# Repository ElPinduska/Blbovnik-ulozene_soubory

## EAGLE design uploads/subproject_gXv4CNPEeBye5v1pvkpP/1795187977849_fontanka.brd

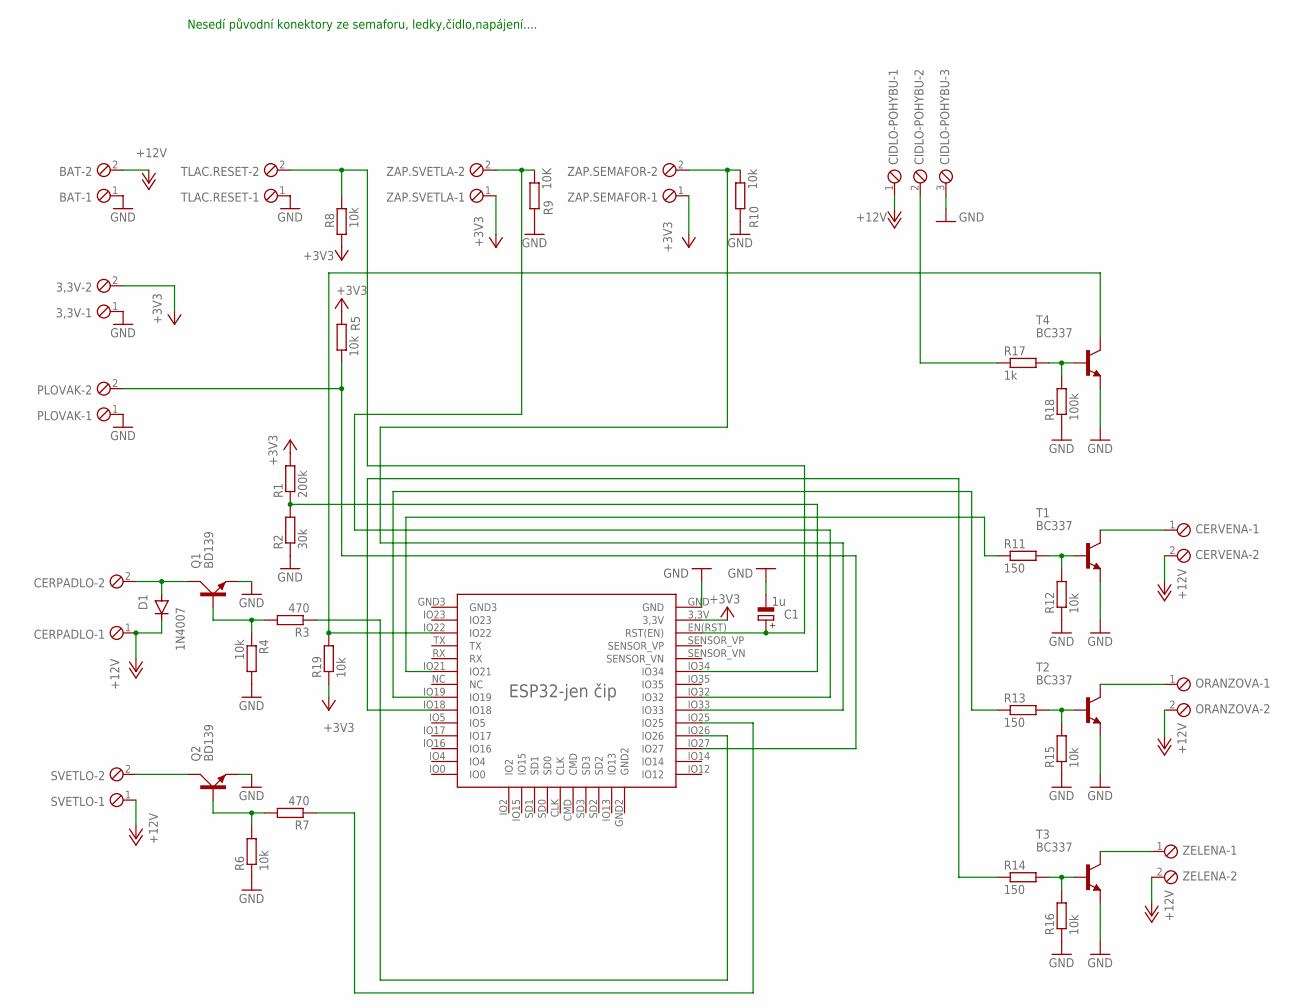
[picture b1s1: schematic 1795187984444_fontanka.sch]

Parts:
3,3V: MPT2; 2POL254
BAT: MPT2; 2POL254
C1: 1u; E2,5-6E
CERPADLO: MPT2; 2POL254
CERVENA: MPT2; 2POL254
CIDLO-POHYBU: MPT3; 3POL254
D1: 1N4007; DO41-10
ORANZOVA: MPT2; 2POL254
PLOVAK: MPT2; 2POL254
Q1, Q2: BD139; TO126AV
R1: 200k; 0204/7
R2: 30k; 0204/7
R3, R7: 470; 0204/7
R4, R5, R6, R8, R10, R12, R15, R16, R19: 10k; 0204/7
R9: 10K; 0204/7
R11, R13, R14: 150; 0204/7
R17: 1k; 0204/7
R18: 100k; 0204/7
SVETLO: MPT2; 2POL254
T1, T2, T3, T4: BC337; TO92-CBE
TLAC.RESET: MPT2; 2POL254
U$2: ESP32-PATICEESP32-2,54PIN; ESP32-PATICE2,54
ZAP.SEMAFOR, ZAP.SVETLA: MPT2; 2POL254
ZELENA: MPT2; 2POL254

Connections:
+3V3: 3,3V.2, R1.2, R5.2, R8.1, R19.1, U$2.3,3V, ZAP.SEMAFOR.1, ZAP.SVETLA.1
+12V: BAT.2, CERPADLO.1, CERVENA.2, CIDLO-POHYBU.1, D1.C, ORANZOVA.2, SVETLO.1, ZELENA.2
GND: 3,3V.1, BAT.1, C1.-, CIDLO-POHYBU.3, PLOVAK.1, Q1.E, Q2.E, R2.1, R4.2, R6.1, R9.1, R10.1, R12.1, R15.1, R16.1, R18.1, T1.E, T2.E, T3.E, T4.E, TLAC.RESET.1, U$2.GND
unnamed: R1.1, R2.2, U$2.IO34
unnamed: R3.1, U$2.IO26
unnamed: Q1.B, R3.2, R4.1
unnamed: CERPADLO.2, D1.A, Q1.C
unnamed: R19.2, T4.C, U$2.IO22
unnamed: R11.1, U$2.IO21
unnamed: PLOVAK.2, R5.1, U$2.IO27
unnamed: C1.+, R8.2, TLAC.RESET.2, U$2.EN(RST) (RST(EN))
unnamed: R7.1, U$2.IO25
unnamed: Q2.B, R6.2, R7.2
unnamed: R9.2, U$2.IO32, ZAP.SVETLA.2
unnamed: R10.2, U$2.IO33, ZAP.SEMAFOR.2
unnamed: R11.2, R12.2, T1.B
unnamed: R13.1, U$2.IO19
unnamed: R14.1, U$2.IO18
unnamed: R13.2, R15.2, T2.B
unnamed: R14.2, R16.2, T3.B
unnamed: T3.C, ZELENA.1
unnamed: ORANZOVA.1, T2.C
unnamed: CERVENA.1, T1.C
unnamed: R17.2, R18.2, T4.B
unnamed: CIDLO-POHYBU.2, R17.1
SVETLO: Q2.C, SVETLO.2

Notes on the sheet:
Nesedí původní konektory ze semaforu, ledky,čidlo,napájení....

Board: 2 copper layers, 40 parts (0 on the bottom side), 26 nets, no tracks yet.

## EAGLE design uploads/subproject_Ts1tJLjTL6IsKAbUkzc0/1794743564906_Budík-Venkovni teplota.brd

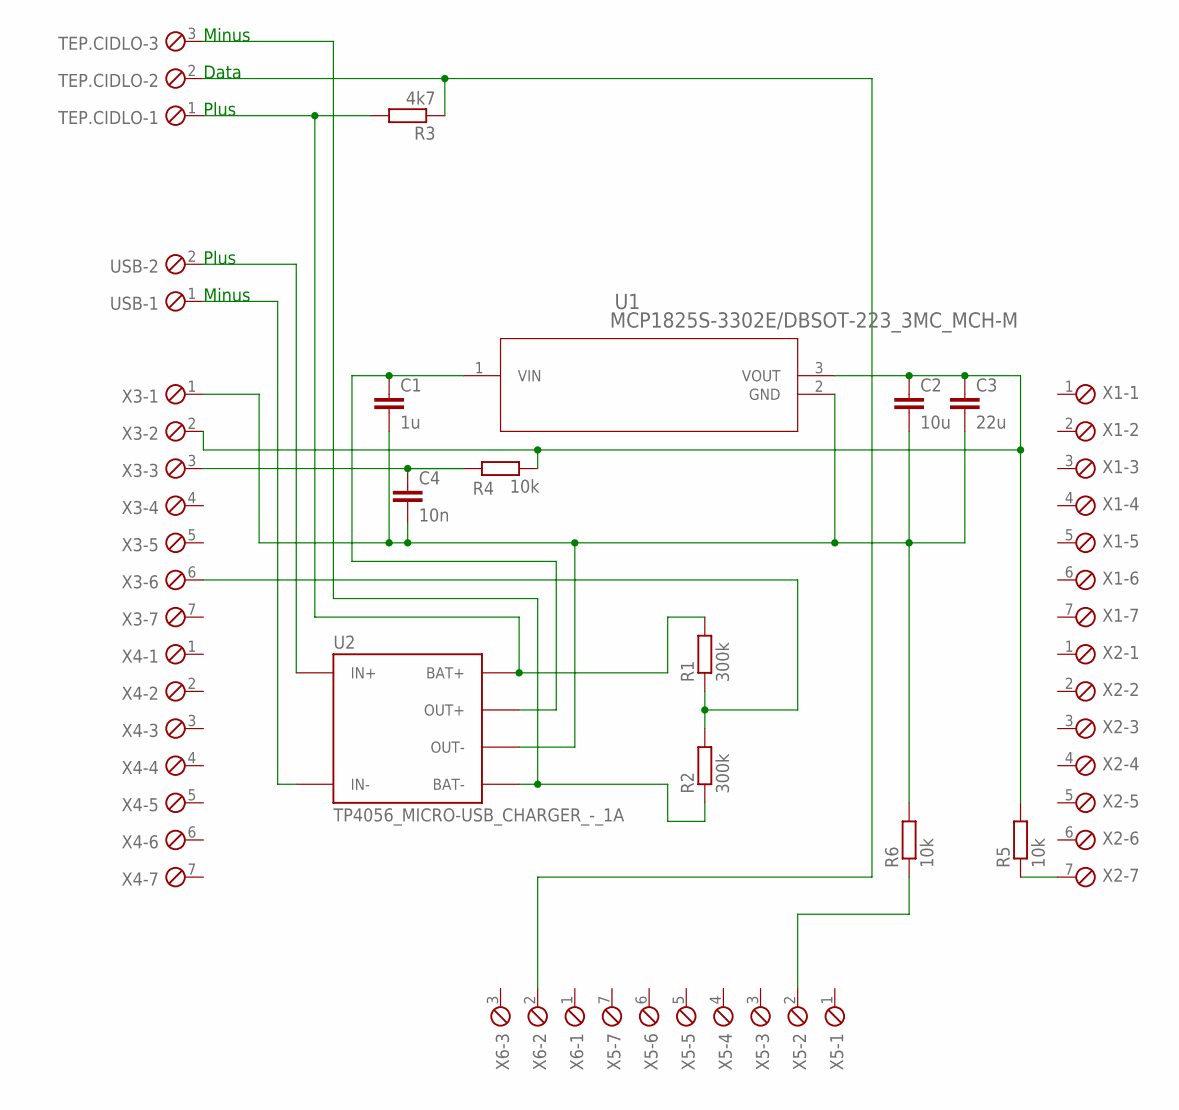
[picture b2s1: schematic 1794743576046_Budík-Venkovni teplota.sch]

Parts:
C1: 1u; C0805
C2: 10u; C0805
C3: 22u; C0805
C4: 10n; C0805
R1, R2: 300k; 0204/7
R3: 4k7; 0204/7
R4, R5, R6: 10k; 0204/7
TEP.CIDLO: MPT3; 3POL254
U1: MCP1825S-3302E/DBSOT-223_3MC_MCH-M; SOT-223_3MC_MCH-M
U2: TP4056_MICRO-USB_CHARGER_-_1A; MODULE_TP4056_MICRO-USB_CHARGER_-_1A
USB: MPT2; 2POL254
X1, X2, X3, X4, X5: MPT7; 7POL254
X6: MPT3; 3POL254

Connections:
unnamed: U2.IN_N (IN-), USB.1
unnamed: U2.IN_P (IN+), USB.2
unnamed: R1.2, R3.2, TEP.CIDLO.1, U2.BAT_P (BAT+)
unnamed: R2.1, TEP.CIDLO.3, U2.BAT_N (BAT-)
unnamed: C1.1, U1.1 (VIN), U2.OUT_P (OUT+)
unnamed: C1.2, C2.2, C3.2, C4.2, R6.2, U1.2 (GND), U2.OUT_N (OUT-), X3.1
unnamed: C2.1, C3.1, R4.2, R5.2, U1.3 (VOUT), X3.2
unnamed: R1.1, R2.2, X3.6
unnamed: R3.1, TEP.CIDLO.2, X6.2
unnamed: C4.1, R4.1, X3.3
unnamed: R5.1, X2.7
unnamed: R6.1, X5.2

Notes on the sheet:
Minus
Plus
Data

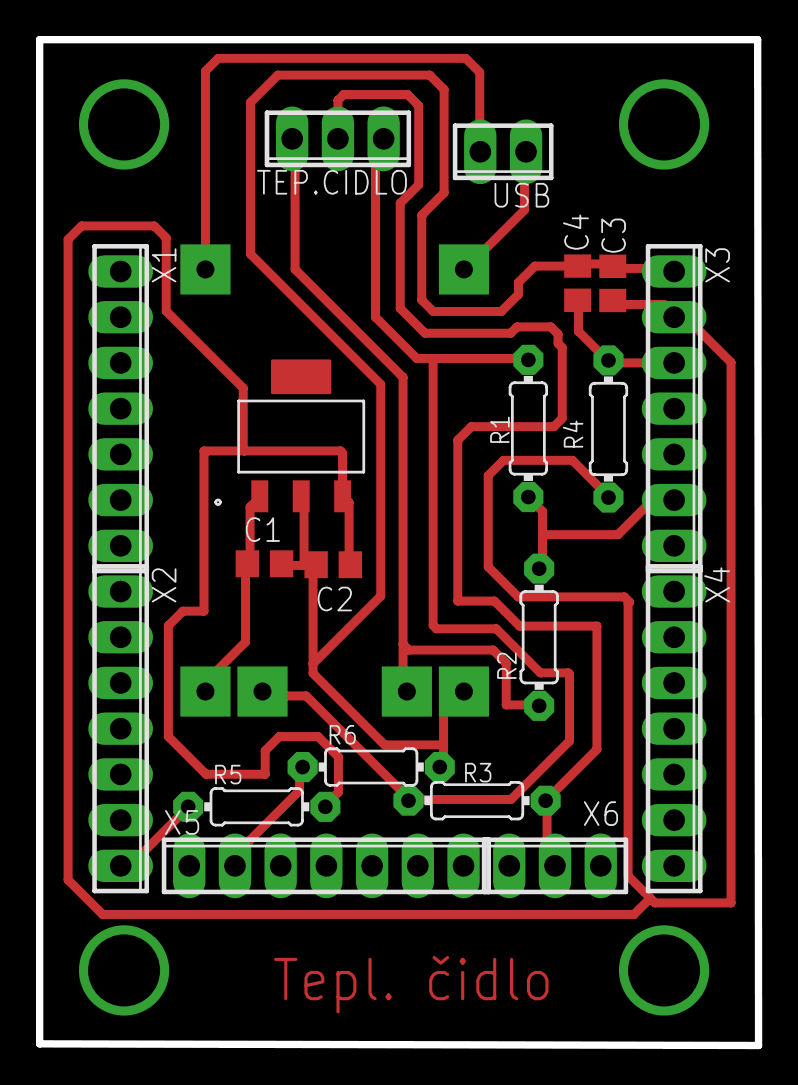
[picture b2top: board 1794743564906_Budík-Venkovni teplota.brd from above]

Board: 2 copper layers, 39.9 x 55.9 mm, 20 parts (1 on the bottom side), 12 nets.

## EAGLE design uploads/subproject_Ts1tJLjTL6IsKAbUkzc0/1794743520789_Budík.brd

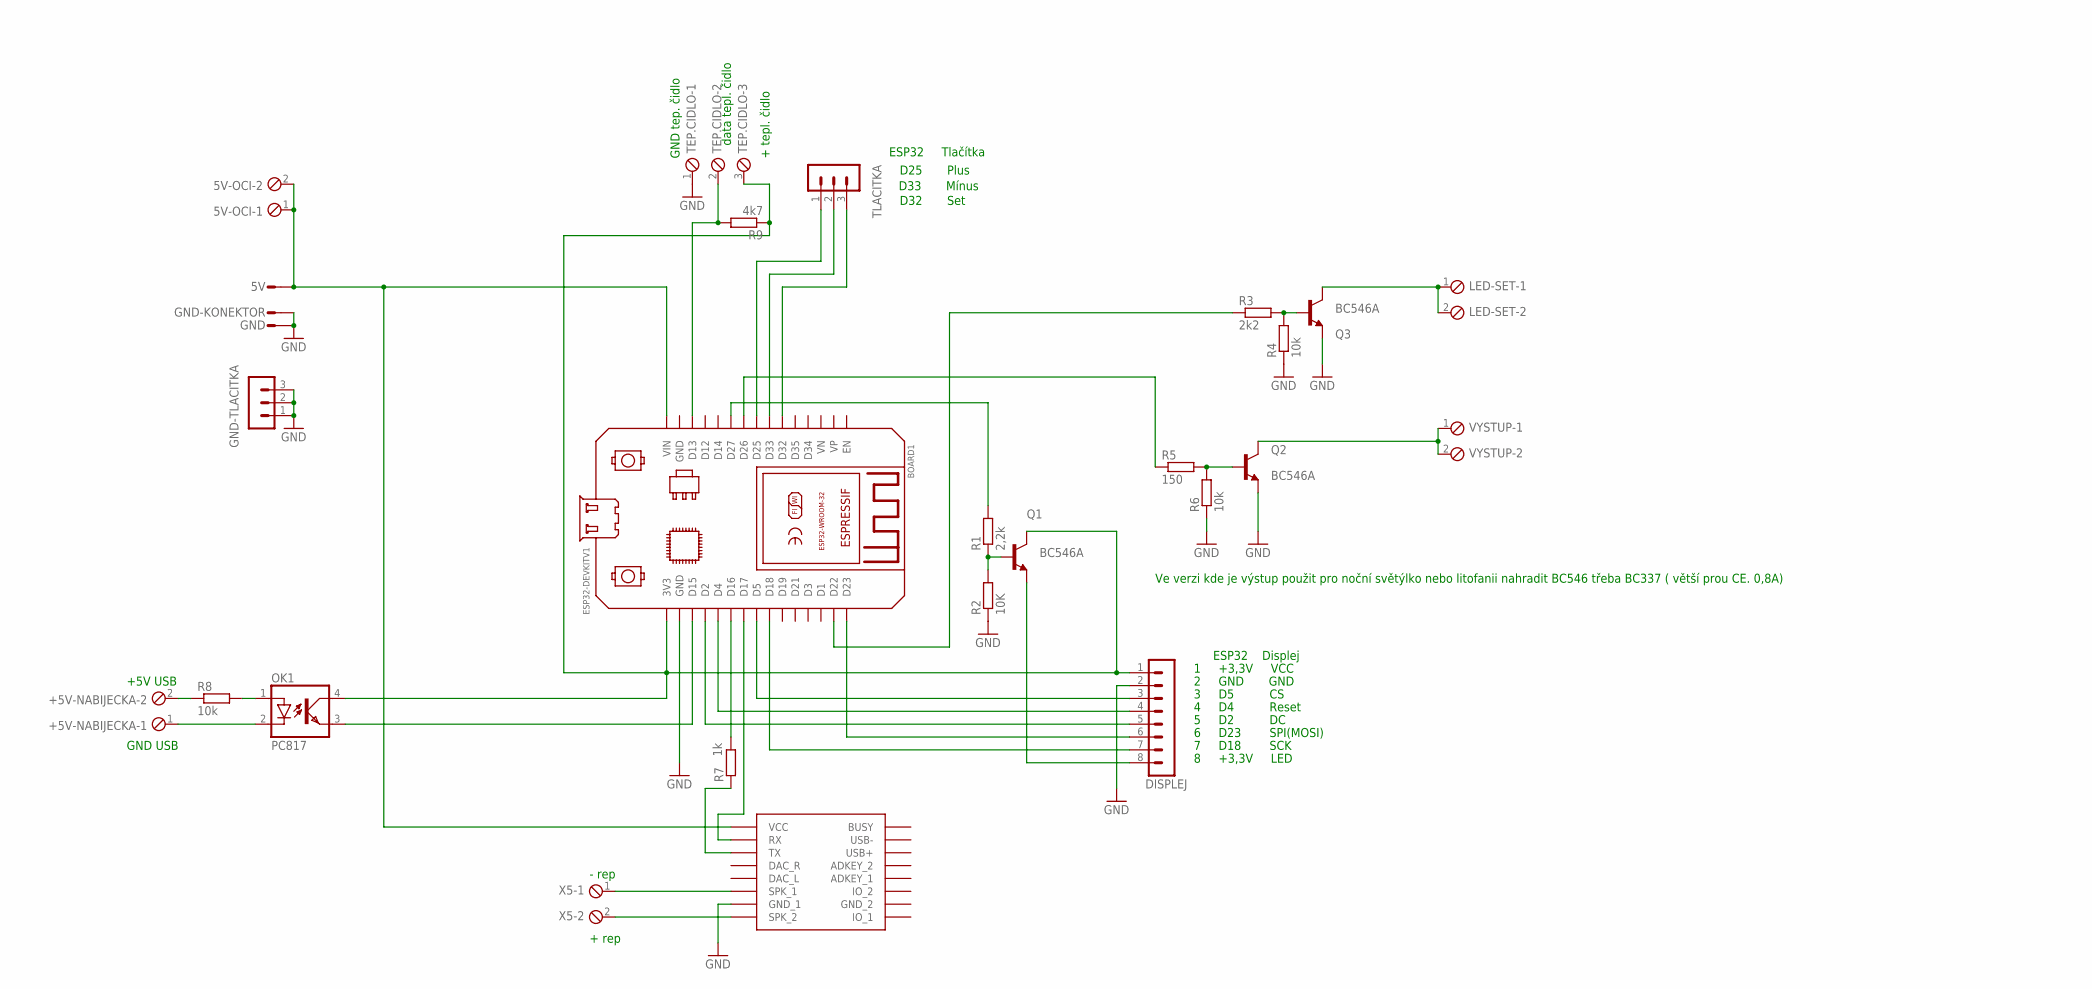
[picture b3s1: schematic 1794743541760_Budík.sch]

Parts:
5V: ST2,8
5V-OCI: MPT2; 2POL254
+5V-NABIJECKA: MPT2; 2POL254
BOARD1: ESP32DEVKITV1; ESP32-DEVKITV1
DISPLEJ: MA08-1
GND: ST2,8
GND-KONEKTOR: ST2,8
GND-TLACITKA: MA03-1
LED-SET: MPT2; 2POL254
OK1: PC817; DIL04
Q1, Q2, Q3: BC546A; TO92-EBC
R1: 2,2k; 0204/7
R2: 10K; 0204/7
R3: 2k2; 0204/7
R4, R6, R8: 10k; 0204/7
R5: 150; 0204/7
R7: 1k; 0204/7
R9: 4k7; 0204/7
TEP.CIDLO: MPT3; 3POL254
TLACITKA: MA03-1
U$1: DFPLAYER
VYSTUP: MPT2; 2POL254
X5: MPT2; 2POL254

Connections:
GND: BOARD1.GND@1 (GND), DISPLEJ.2, GND.1, GND-KONEKTOR.1, GND-TLACITKA.1, GND-TLACITKA.2, GND-TLACITKA.3, Q2.E, Q3.E, R2.1, R4.1, R6.1, TEP.CIDLO.1, U$1.GND_1
unnamed: 5V.1, 5V-OCI.1, 5V-OCI.2, BOARD1.VIN, U$1.VCC
unnamed: Q3.B, R3.2, R4.2
unnamed: Q2.B, R5.2, R6.2
unnamed: +5V-NABIJECKA.2, R8.1
unnamed: OK1.1 (A), R8.2
unnamed: U$1.SPK1 (SPK_1), X5.1
unnamed: U$1.SPK2 (SPK_2), X5.2
unnamed: BOARD1.3V3, DISPLEJ.1, OK1.4 (COL), Q1.C, R9.1, TEP.CIDLO.3
unnamed: BOARD1.D15, OK1.3 (EMIT)
unnamed: BOARD1.D5, DISPLEJ.3
unnamed: BOARD1.D4, DISPLEJ.4
unnamed: BOARD1.D2, DISPLEJ.5
unnamed: BOARD1.D23, DISPLEJ.6
unnamed: BOARD1.D18, DISPLEJ.7
unnamed: DISPLEJ.8, Q1.E
unnamed: R7.1, U$1.TX
unnamed: BOARD1.D17, U$1.RX
unnamed: BOARD1.D16, R7.2
unnamed: BOARD1.D13, R9.2, TEP.CIDLO.2
unnamed: BOARD1.D25, TLACITKA.1
unnamed: BOARD1.D33, TLACITKA.2
unnamed: BOARD1.D32, TLACITKA.3
unnamed: BOARD1.D27, R1.2
unnamed: Q1.B, R1.1, R2.2
unnamed: BOARD1.D22, R3.1
unnamed: BOARD1.D26, R5.1
unnamed: Q2.C, VYSTUP.1, VYSTUP.2
unnamed: LED-SET.1, LED-SET.2, Q3.C
unnamed: +5V-NABIJECKA.1, OK1.2 (C)

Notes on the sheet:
ESP32 Displej
1 +3,3V VCC
2 GND GND
3 D5 CS
4 D4 Reset
5 D2 DC
6 D23 SPI(MOSI)
7 D18 SCK
8 +3,3V LED
ESP32 Tlačítka
D25 Plus
D33 Mínus
D32 Set
+5V USB
GND USB
- rep
+ rep
GND tep. čidlo
data tepl. čidlo
+ tepl. čidlo
Ve verzi kde je výstup použit pro noční světýlko nebo litofanii nahradit BC546 třeba BC337 ( větší prou CE. 0,8A)

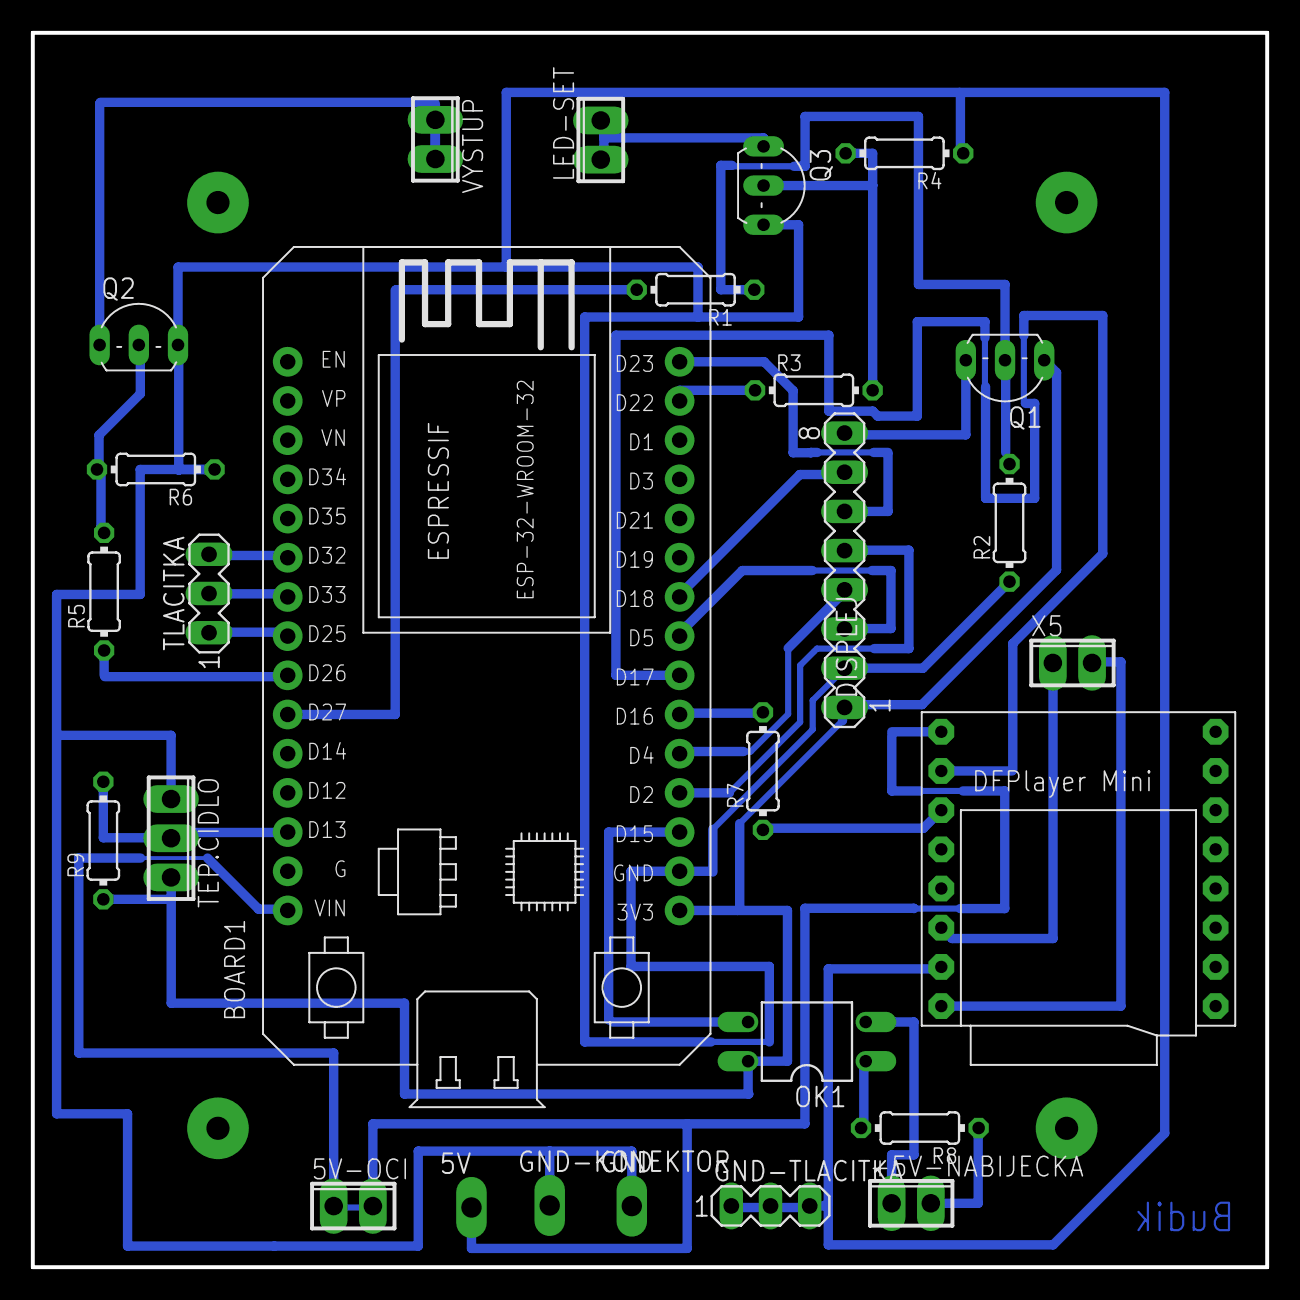
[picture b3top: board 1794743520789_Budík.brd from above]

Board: 2 copper layers, 80.0 x 80.0 mm, 27 parts (0 on the bottom side), 30 nets.

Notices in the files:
parts and their libraries:
COPYRIGHT: Copyright (C) 2026 Ultra Librarian. All rights reserved.
